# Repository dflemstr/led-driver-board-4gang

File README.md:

# LED Driver Board (4-gang)

This is a simple LED driver board for 4x 5V neopixel-style LED strips, with level shifters to allow for 3.3V logic.

All of this could probably be soldered-together by hand using an off-the-shelf level shifter PCB and some wires, but
I wanted the convenience of having everything mounted to a single board.

The design also offers a shared fuse for all the LED outputs, which is a nice added benefit.  However, the fuse holder
can be skipped and replaced by a short wire if so desired.

## Tradrack mount

The `./tradrack-mount` folder contains a simple model to mount the board to an Annex Engineering TradRack, or on
the underside of any 2020 aluminium extrusion, really.  I recommend setting `Perimeters & Shell` > `Advanced` >
`No perimeters on bridge areas` > `Fill the voids with bridges` in SuperSlicer to make the mounting screw holes turn out
OK; I couldn't be bothered to model a more fancy hole.

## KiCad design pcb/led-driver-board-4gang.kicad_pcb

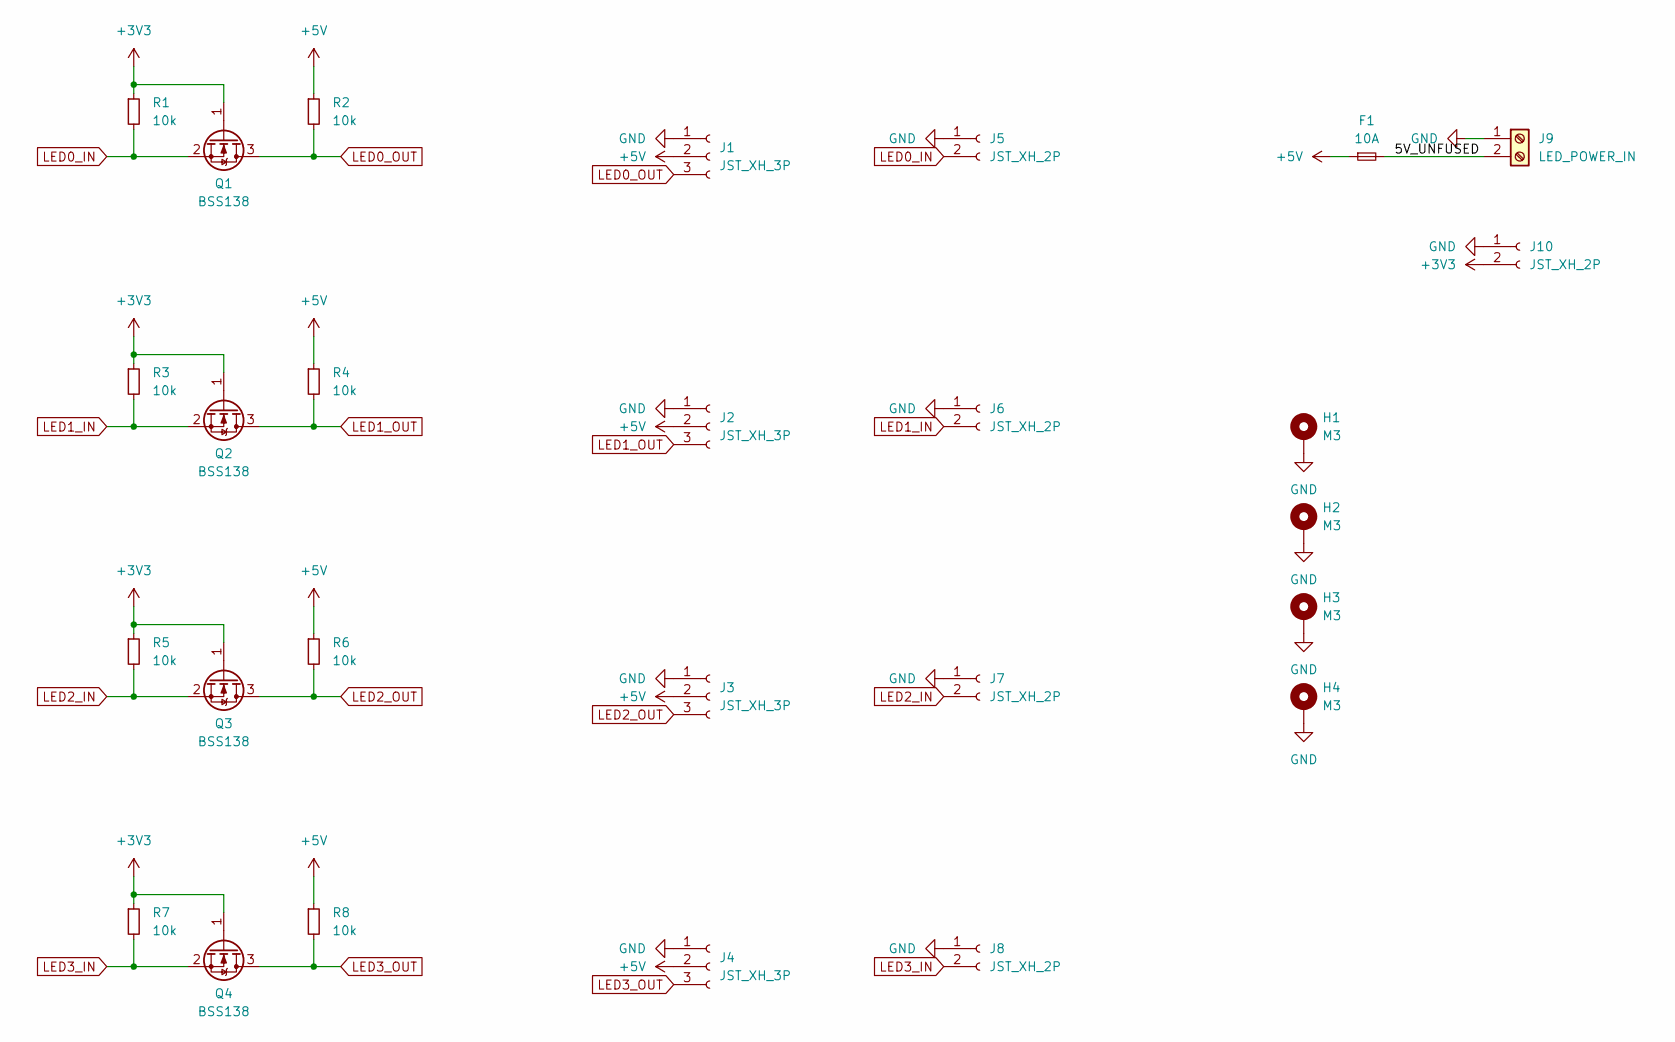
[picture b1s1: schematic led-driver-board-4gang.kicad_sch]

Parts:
F1: 10A; Fuseholder_Blade_Mini_Keystone_3568; LCSC C3206309
H1, H2, H3, H4: M3; MountingHole_3.2mm_M3_Pad_Via
J1, J2, J3, J4: JST_XH_3P; JST_XH_B3B-XH-A_1x03_P2.50mm_Vertical; LCSC C144394
J5, J6, J7, J8, J10: JST_XH_2P; JST_XH_B2B-XH-A_1x02_P2.50mm_Vertical; LCSC C158012
J9: LED_POWER_IN; TerminalBlock_Philmore_TB132_1x02_P5.00mm_Horizontal; LCSC C557651
Q1, Q2, Q3, Q4: BSS138; SOT-23; LCSC C112239
R1, R2, R3, R4, R5, R6, R7, R8: 10k; R_0805_2012Metric; LCSC C17414

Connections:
+3V3: J10.2, Q1.1 (G), Q2.1 (G), Q3.1 (G), Q4.1 (G), R1.1, R3.1, R5.1, R7.1
+5V: F1.1, J1.2, J2.2, J3.2, J4.2, R2.1, R4.1, R6.1, R8.1
/5V_UNFUSED: F1.2, J9.2
GND: H1.1, H2.1, H3.1, H4.1, J1.1, J2.1, J3.1, J4.1, J5.1, J6.1, J7.1, J8.1, J9.1, J10.1
LED0_IN: J5.2, Q1.2 (S), R1.2
LED0_OUT: J1.3, Q1.3 (D), R2.2
LED1_IN: J6.2, Q2.2 (S), R3.2
LED1_OUT: J2.3, Q2.3 (D), R4.2
LED2_IN: J7.2, Q3.2 (S), R5.2
LED2_OUT: J3.3, Q3.3 (D), R6.2
LED3_IN: J8.2, Q4.2 (S), R7.2
LED3_OUT: J4.3, Q4.3 (D), R8.2

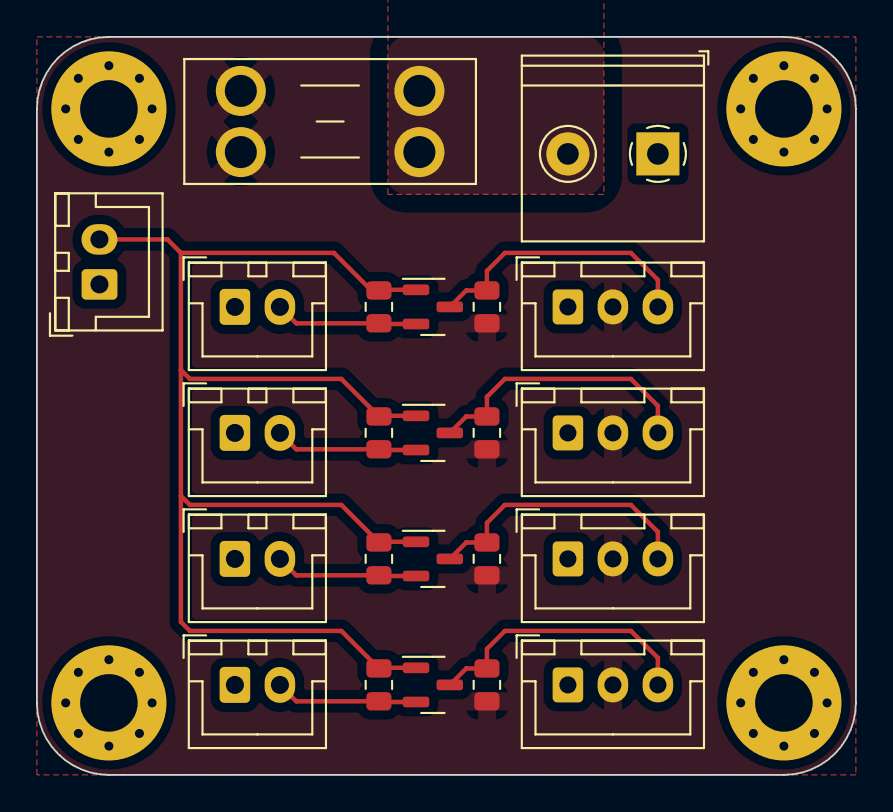
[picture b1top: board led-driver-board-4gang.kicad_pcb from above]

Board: 2 copper layers, 45.5 x 41.0 mm, 27 parts (0 on the bottom side), 12 nets.

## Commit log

2024-02-05 Initial PCB and mounting solution
2024-02-05 Add readme
2024-02-05 Add bit to README about the TradRack mount
